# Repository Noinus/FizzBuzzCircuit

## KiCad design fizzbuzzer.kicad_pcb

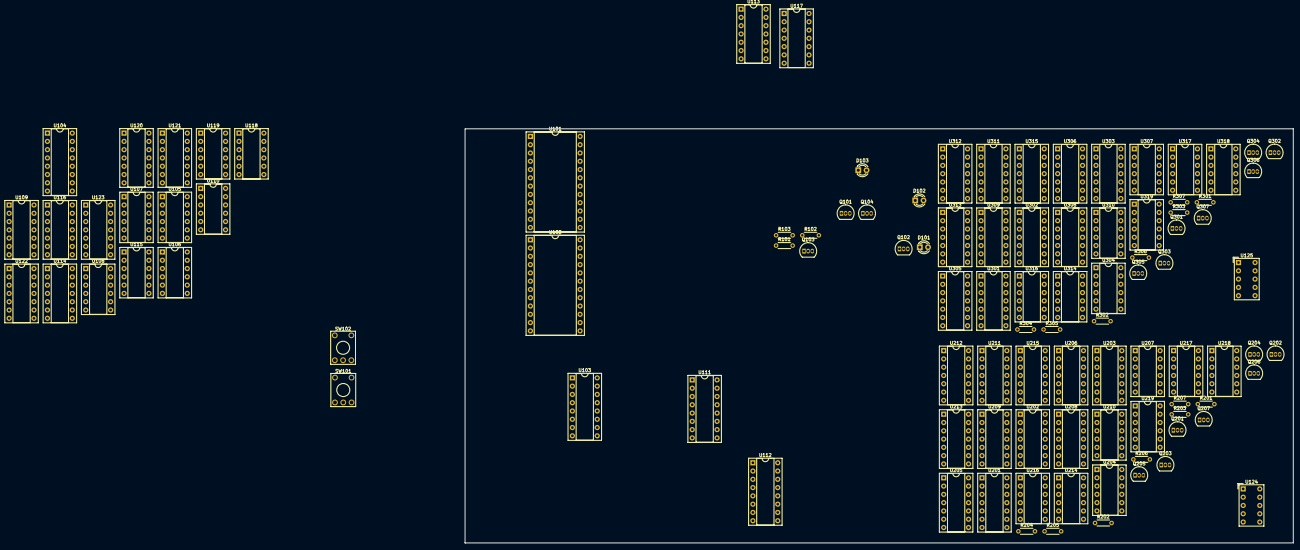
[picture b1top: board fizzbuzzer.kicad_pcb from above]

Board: 2 copper layers, 254.0 x 127.0 mm, 103 parts (0 on the bottom side), 220 nets, no tracks yet.

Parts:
D101, D102, D103: LED; LED_D3.0mm
Q101, Q102, Q103, Q201, Q202, Q203, Q204, Q205, Q206, Q207, Q301, Q302, Q303, Q304, Q305, Q306, Q307: Q_NMOS_DGS; TO-92_Inline
Q104: Q_PMOS_DGS; TO-92_Inline
R101, R102, R103, R201, R202, R203, R204, R205, R206, R207, R301, R302, R303, R304, R305, R306, R307: 470; R_Axial_DIN0204_L3.6mm_D1.6mm_P5.08mm_Horizontal
SW101, SW102: SW_Coded_SH-7070; KSA_Tactile_SPST
U101, U102: 74LS154; DIP-24_W15.24mm_Socket
U103, U104, U111, U112: 74LS83; DIP-16_W7.62mm_Socket
U105, U106, U107, U108, U110, U115, U118, U119, U204, U207, U210, U214, U216, U217, U218, U219, U304, U307, U310, U314, U316, U317, U318, U319: 4072; DIP-12_W7.62mm_Socket
U109, U201, U301: 74LS04; DIP-14_W7.62mm_Socket
U113, U114, U116, U117, U121, U122, U123, U205, U209, U211, U212, U213, U215, U305, U309, U311, U312, U313, U315: 4081; DIP-14_W7.62mm_Socket
U120: 74HC86; DIP-14_W7.62mm_Socket
U124, U125: HDSP-7401
U202, U203, U206, U208, U302, U303, U306, U308: 4073; DIP-14_W7.62mm_Socket

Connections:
/hex_to_7seg1/A: R301.2, U125.10 (A)
/hex_to_7seg1/B: R302.2, U125.9 (B)
/hex_to_7seg1/C: R303.2, U125.8 (C)
/hex_to_7seg1/D: R304.2, U125.5 (D)
/hex_to_7seg1/E: R305.2, U125.4 (E)
/hex_to_7seg1/F: R306.2, U125.2 (F)
/hex_to_7seg1/G: R307.2, U125.3 (G)
/hex_to_7seg/A: R201.2, U124.10 (A)
/hex_to_7seg/B: R202.2, U124.9 (B)
/hex_to_7seg/C: R203.2, U124.8 (C)
/hex_to_7seg/D: R204.2, U124.5 (D)
/hex_to_7seg/E: R205.2, U124.4 (E)
/hex_to_7seg/EN: Q104.3 (S), Q201.1 (D), Q202.1 (D), Q203.1 (D), Q204.1 (D), Q205.1 (D), Q206.1 (D), Q207.1 (D), Q301.1 (D), Q302.1 (D), Q303.1 (D), Q304.1 (D), Q305.1 (D), Q306.1 (D), Q307.1 (D)
/hex_to_7seg/F: R206.2, U124.2 (F)
/hex_to_7seg/G: R207.2, U124.3 (G)
GND: D101.1 (K), D102.1 (K), D103.1 (K), U101.12 (GND), U102.12 (GND), U103.12 (GND), U104.12 (GND), U105.7 (VSS), U106.4, U106.5, U106.7 (VSS), U107.7 (VSS), U108.4, U108.5, U108.7 (VSS), U110.4, U110.5, U110.7 (VSS), U110.11, U110.12, U111.1 (A4), U111.3 (A3), U111.8 (A2), U111.12 (GND), U112.12 (GND), U114.7 (VSS), U115.5, U115.7 (VSS), U115.12, U116.7 (VSS), U117.7 (VSS), U118.4, U118.5, U118.7 (VSS), U118.12, U119.5, U119.12, U120.7 (GND), U121.7 (VSS), U124.1 (CA), U124.6 (CA), U124.7 (DP), U125.1 (CA), U125.6 (CA), U125.7 (DP), U201.7 (GND), U202.7 (VSS), U204.5, U204.7 (VSS), U204.12, U205.7 (VSS), U207.4, U207.5, U208.7 (VSS), U210.11, U210.12, U214.4, U214.5, U216.4, U216.5, U217.12, U218.4, U218.5, U218.11, U218.12, U219.4, U219.5, U219.7 (VSS), U301.7 (GND), U302.7 (VSS), U304.5, U304.7 (VSS), U304.12, U305.7 (VSS), U307.4, U307.5, U308.7 (VSS), U310.11, U310.12, U314.4, U314.5, U316.4, U316.5, U317.12, U318.4, U318.5, U318.11, U318.12, U319.4, U319.5, U319.7 (VSS)
unnamed: D101.2 (A), Q101.3 (S)
unnamed: D102.2 (A), Q102.3 (S)
unnamed: D103.2 (A), Q103.3 (S)
unnamed: Q101.1 (D), R101.1
unnamed: Q101.2 (G), U119.9, U121.3
unnamed: Q102.1 (D), R102.1
unnamed: Q102.2 (G), U117.4, U119.10
unnamed: Q103.1 (D), R103.1
unnamed: Q103.2 (G), U116.10, U119.11
unnamed: Q201.2 (G), U207.1
unnamed: Q201.3 (S), R201.1
unnamed: Q202.3 (S), R202.1
unnamed: Q203.2 (G), U214.1
unnamed: Q203.3 (S), R203.1
unnamed: Q204.2 (G), U216.1
unnamed: Q204.3 (S), R204.1
unnamed: Q205.3 (S), R205.1
unnamed: Q206.2 (G), U218.1
unnamed: Q206.3 (S), R206.1
unnamed: Q207.3 (S), R207.1
unnamed: Q301.2 (G), U307.1
unnamed: Q301.3 (S), R301.1
unnamed: Q302.3 (S), R302.1
unnamed: Q303.2 (G), U314.1
unnamed: Q303.3 (S), R303.1
unnamed: Q304.2 (G), U316.1
unnamed: Q304.3 (S), R304.1
unnamed: Q305.3 (S), R305.1
unnamed: Q306.2 (G), U318.1
unnamed: Q306.3 (S), R306.1
unnamed: Q307.3 (S), R307.1
unnamed: U101.2 (S1), U105.2
unnamed: U101.3 (S2), U105.3
unnamed: U101.4 (S3), U105.9
unnamed: U101.5 (S4), U105.4
unnamed: U101.6 (S5), U105.10
unnamed: U101.7 (S6), U105.11
unnamed: U101.8 (S7), U106.9
unnamed: U101.9 (S8), U105.5
unnamed: U101.10 (S9), U105.12
unnamed: U101.11 (S10), U106.2
unnamed: U101.13 (S11), U106.10
unnamed: U101.14 (S12), U106.3
unnamed: U101.15 (S13), U106.11
unnamed: U101.16 (S14), U106.12
unnamed: U102.2 (S1), U107.9
unnamed: U102.3 (S2), U107.10
unnamed: U102.4 (S3), U107.2
unnamed: U102.5 (S4), U107.11
unnamed: U102.6 (S5), U107.3
unnamed: U102.7 (S6), U107.4
unnamed: U102.8 (S7), U108.9
unnamed: U102.9 (S8), U107.12
unnamed: U102.10 (S9), U107.5
unnamed: U102.11 (S10), U110.9
unnamed: U102.13 (S11), U108.10
unnamed: U102.14 (S12), U110.10
unnamed: U102.15 (S13), U108.11
unnamed: U102.16 (S14), U108.12
unnamed: U103.2 (S3), U109.5
unnamed: U103.6 (S2), U109.3
unnamed: U103.9 (S1), U109.1
unnamed: U103.15 (S4), U109.9
unnamed: U104.2 (S3), U112.3 (A3)
unnamed: U104.6 (S2), U112.8 (A2)
unnamed: U104.9 (S1), U112.10 (A1)
unnamed: U104.15 (S4), U112.1 (A4)
unnamed: U106.1, U108.3
unnamed: U107.1, U110.2
unnamed: U109.2, U111.11 (B1)
unnamed: U109.4, U111.7 (B2)
unnamed: U109.6, U111.4 (B3)
unnamed: U109.7 (GND), U113.7 (VSS), U119.7 (VSS)
unnamed: U109.8, U111.16 (B4)
unnamed: U109.10, U121.2
unnamed: U109.12, U117.6
unnamed: U111.2 (S3), U112.4 (B3)
unnamed: U111.6 (S2), U112.7 (B2)
unnamed: U111.9 (S1), U112.11 (B1)
unnamed: U111.15 (S4), U112.13 (C0)
unnamed: U112.2 (S3), U116.2
unnamed: U112.6 (S2), U116.5
unnamed: U112.9 (S1), U116.1
unnamed: U112.15 (S4), U116.6
unnamed: U113.3, U115.2
unnamed: U113.4, U115.3
unnamed: U113.10, U115.4
unnamed: U113.11, U115.9
unnamed: U114.3, U115.10
unnamed: U114.4, U115.11
unnamed: U114.10, U119.2
unnamed: U114.11, U119.3
unnamed: U115.1, U118.10
unnamed: U116.3, U118.2
unnamed: U116.4, U118.3
unnamed: U117.3, U119.4
unnamed: U118.9, U119.1
unnamed: U201.2, U202.13, U203.13, U205.2, U205.9, U206.13, U209.6, U212.9, U212.13, U213.2, U213.6, U215.13
unnamed: U201.4, U202.8, U202.12, U203.4, U206.4, U208.5, U208.8, U209.2, U209.9, U211.1, U211.13, U213.1
unnamed: U201.6, U202.2, U203.12, U205.1, U206.1, U209.1, U209.5, U211.9, U212.12, U213.9, U215.2, U215.8
unnamed: U201.8, U202.3, U202.11, U203.1, U203.11, U205.5, U208.1, U208.3, U209.8, U209.12, U211.5
unnamed: U202.6, U204.3
unnamed: U202.9, U204.2
unnamed: U202.10, U207.9
unnamed: U203.6, U207.11
unnamed: U203.9, U207.10
unnamed: U203.10, U214.9
unnamed: U204.1, U207.2
unnamed: U204.4, U205.3
unnamed: U204.9, U205.4
unnamed: U204.10, U205.10
unnamed: U204.11, U205.11
unnamed: U206.6, U214.11
unnamed: U206.9, U214.10
unnamed: U206.10, U214.12
unnamed: U207.12, U209.3
unnamed: U208.6, U217.2
unnamed: U208.9, U217.9
unnamed: U209.4, U210.10
unnamed: U209.10, U210.2
unnamed: U209.11, U210.3
unnamed: U210.1, U214.2
unnamed: U210.4, U211.3
unnamed: U210.5, U211.4
unnamed: U211.10, U214.3
unnamed: U211.11, U216.3
unnamed: U212.3, U216.9
unnamed: U212.4, U216.10
unnamed: U212.10, U216.11
unnamed: U212.11, U216.12
unnamed: U213.3, U217.3
unnamed: U213.4, U217.4
unnamed: U213.10, U217.5
unnamed: U213.11, U218.3
unnamed: U215.3, U217.10
unnamed: U215.4, U217.11
unnamed: U215.10, U219.2
unnamed: U215.11, U219.3
unnamed: U217.1, U218.2
unnamed: U218.10, U219.1
unnamed: U301.2, U302.13, U303.13, U305.2, U305.9, U306.13, U309.6, U312.9, U312.13, U313.2, U313.6, U315.13
unnamed: U301.4, U302.8, U302.12, U303.4, U306.4, U308.5, U308.8, U309.2, U309.9, U311.1, U311.13, U313.1
unnamed: U301.6, U302.2, U303.12, U305.1, U306.1, U309.1, U309.5, U311.9, U312.12, U313.9, U315.2, U315.8
unnamed: U301.8, U302.3, U302.11, U303.1, U303.11, U305.5, U308.1, U308.3, U309.8, U309.12, U311.5
unnamed: U302.6, U304.3
unnamed: U302.9, U304.2
unnamed: U302.10, U307.9
unnamed: U303.6, U307.11
unnamed: U303.9, U307.10
unnamed: U303.10, U314.9
unnamed: U304.1, U307.2
unnamed: U304.4, U305.3
unnamed: U304.9, U305.4
unnamed: U304.10, U305.10
unnamed: U304.11, U305.11
unnamed: U306.6, U314.11
unnamed: U306.9, U314.10
unnamed: U306.10, U314.12
unnamed: U307.12, U309.3
unnamed: U308.6, U317.2
unnamed: U308.9, U317.9
unnamed: U309.4, U310.10
unnamed: U309.10, U310.2
unnamed: U309.11, U310.3
unnamed: U310.1, U314.2
unnamed: U310.4, U311.3
unnamed: U310.5, U311.4
unnamed: U311.10, U314.3
unnamed: U311.11, U316.3
unnamed: U312.3, U316.9
unnamed: U312.4, U316.10
unnamed: U312.10, U316.11
unnamed: U312.11, U316.12
unnamed: U313.3, U317.3
unnamed: U313.4, U317.4
unnamed: U313.10, U317.5
unnamed: U313.11, U318.3
unnamed: U315.3, U317.10
unnamed: U315.4, U317.11
unnamed: U315.10, U319.2
unnamed: U315.11, U319.3
unnamed: U317.1, U318.2
unnamed: U318.10, U319.1
VCC: Q104.1 (D), R101.2, R102.2, R103.2, SW101.C, U101.24 (VCC), U102.24 (VCC), U103.5 (VCC), U104.5 (VCC), U109.14 (VCC), U111.5 (VCC), U111.10 (A1), U112.5 (VCC), U113.14 (VDD), U114.14 (VDD), U116.14 (VDD), U117.14 (VDD), U120.14 (VCC), U121.14 (VDD), U201.14 (VCC), U202.14 (VDD), U205.14 (VDD), U208.14 (VDD), U301.14 (VCC), U302.14 (VDD), U305.14 (VDD), U308.14 (VDD)
bit_0: SW101.1, U101.23 (A0), U103.10 (A1), U201.1, U202.5, U203.5, U203.8, U206.5, U206.8, U209.13, U211.2, U215.6
bit_1: SW101.2, U102.23 (A0), U103.8 (A2), U201.3, U203.2, U205.6, U205.13, U206.2, U206.12, U212.2, U212.8, U213.13, U215.9, U215.12
bit_2: SW101.4, U101.22 (A1), U104.10 (A1), U201.5, U202.4, U205.12, U206.3, U206.11, U208.2, U208.4, U211.6, U212.6, U213.5
bit_3: SW101.8, U102.22 (A1), U104.8 (A2), U201.9, U202.1, U203.3, U205.8, U211.8, U211.12, U212.1, U212.5, U213.8, U213.12, U215.1, U215.5
bit_4: SW102.1, U101.21 (A2), U103.11 (B1), U301.1, U302.5, U303.5, U303.8, U306.5, U306.8, U309.13, U311.2, U315.6
bit_5: SW102.2, U102.21 (A2), U103.7 (B2), U301.3, U303.2, U305.6, U305.13, U306.2, U306.12, U312.2, U312.8, U313.13, U315.9, U315.12
bit_6: SW102.4, U101.20 (A3), U104.11 (B1), U301.5, U302.4, U305.12, U306.3, U306.11, U308.2, U308.4, U311.6, U312.6, U313.5
bit_7: U102.20 (A3), U104.7 (B2), U301.9, U302.1, U303.3, U305.8, U311.8, U311.12, U312.1, U312.5, U313.8, U313.12, U315.1, U315.5
div_by_3: U109.13, U116.8, U121.1
div_by_5: U109.11, U116.9, U117.5, U118.1
even_0: U102.1 (S0), U114.5, U117.1
even_1: U113.8, U114.12
even_2: U110.1, U114.8
even_3: U113.12, U114.1
even_4: U102.17 (S15), U113.1, U113.5
odd_0: U101.1 (S0), U114.2, U117.2
odd_1: U105.1, U113.6, U114.13
odd_2: U108.1, U114.9
odd_3: U113.13, U114.6
odd_4: U101.17 (S15), U113.2, U113.9

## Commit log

2021-04-19 init commit
